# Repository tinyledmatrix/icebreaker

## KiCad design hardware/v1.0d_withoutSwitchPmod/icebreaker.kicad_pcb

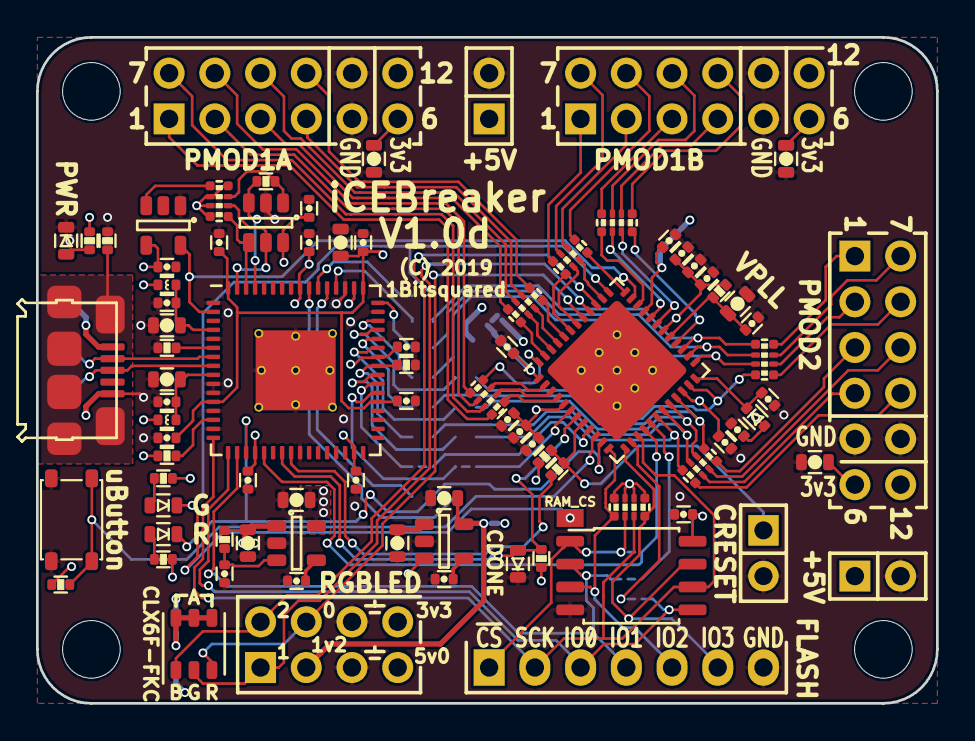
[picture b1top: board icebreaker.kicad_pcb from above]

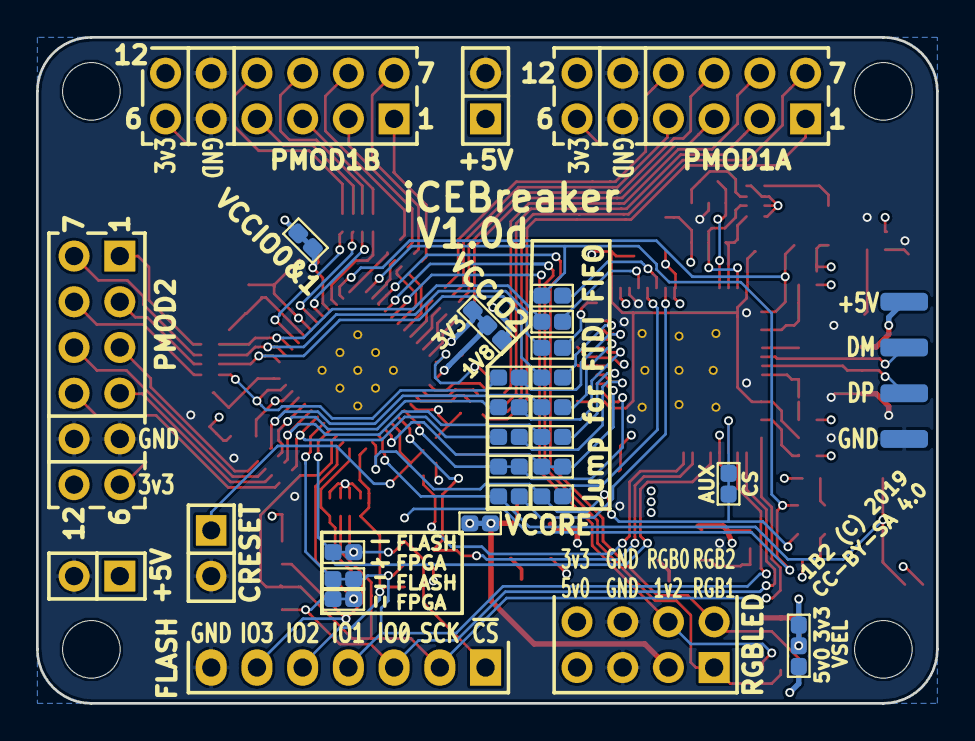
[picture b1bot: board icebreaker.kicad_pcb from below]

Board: 4 copper layers, 50.0 x 37.0 mm, 112 parts (25 on the bottom side), 112 nets.

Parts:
C1, C4, C10, C12, C13, C14, C16, C17, C18, C19, C20, C21, C22, C25, C26, C27, C29, C30, C31, C37: 100n; C_0402
C2, C5, C6, C7, C8, C9, C15: 4u7; C_0603
C3, C11, C28, C38: 10n; C_0402
C23, C36, C39: 1u; C_0402
C24: 10u; C_0603
C32, C33, C34: DNP; C_0603
C35: DNP; C_0402
D1, D4: GRN; D_0603
D2: ~~800mVf; D_SOD-523
D3: BLU; D_0603
D5: RED; D_0603
D11: LED_RGB; LED_Cree_PLCC6_3.4x3.4mm
J1, J2, J15, J16, J18, J29: Jumper; J_NC_0603_15
J3, J4, J5, J6, J7, J8, J9, J10, J11, J12, J13: Jumper; J_0603
J14, J19: Jumper; J_NC_0603_30
J17, J30: Jumper; J_NCNO_0903_30
J20: Flash; Pin_Header_Straight_1x07
J21, J22: PMOD; Socket_Strip_Angled_2x06
J23: PMOD; Socket_Strip_Straight_2x06
J25: RGB Led; Pin_Header_Straight_2x04
J26, J27: 5V AUX; Pin_Header_Straight_2x01
J28: CRESET; PinHeader_2x01_P2.54mm_Vertical
L1, L2: 600; L_0402
P1: pkl_USB_OTG; Connector_USB_Micro_B_SMD
P2, P3, P4, P5: UP; PAD_SMD_1x2.65
P6: RAM_CS; PAD_SMD_1x1.5
R1: 1M; R_0402
R2, R11: 10k; R_Array_Convex_4x0402
R3, R9, R13, R19, R25: 10k; R_0402
R4, R20, R21, R22, R23, R24: 33E; R_Array_Convex_4x0402
R5, R14, R15: 330E; R_0402
R6, R12, R26: 2k2; R_0402
R8: 12k; R_0402
R10: 100E; R_0402
SW1: TACT; SW_SPST_3x4x2.5
U1: 93C46B-SOT-23-6; SOT-23-6
U2: 3.3V; SOT-23-5
U3: 1V2; SOT-23-5
U4: FT2232H; QFN-64-4.45mm1EP_9x9mm_Pitch0.5mm
U5: W25Q; SOIC-8_5.3x5.3mm_Pitch1.27mm
U6: ICE5LP4K-SG48; QFN-48-1EP_7x7mm_Pitch0.5mm
U7: 12MHz; SOT-23-5

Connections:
+1V2: C15.1, J14.2, J25.3, U3.5
+1V8: C7.1, C10.1, C14.1, C16.1, C17.1, J17.3, U4.12, U4.37, U4.49, U4.64
+3V3: C1.1, C4.1, C5.1, C18.1, C19.1, C20.1, C21.1, C22.1, C29.1, C32.2, C33.2, C34.2, D2.A, J17.1, J19.2, J21.6, J21.12, J22.6, J22.12, J23.6, J23.12, J25.8, J30.1, L1.1, L2.1, R2.2, R2.4, R2.6, R2.7, R5.1, R9.2, R11.1, R11.3, R11.5, R11.7, R12.1, R13.2, R14.2, R15.2, R19.1, U1.6, U2.5, U4.20, U4.31, U4.42, U4.50, U4.56, U5.8, U7.4
+5V: C2.1, C8.1, J25.7, J26.1, J27.1, J30.3, P1.1, P2.1, R3.1, U2.1, U3.1, U3.3
/FLASH_CS: J18.1, J20.1, R11.6, U5.1
/FLASH_MISO|IO1: J16.2, J20.4, U4.18, U5.2
/FLASH_MOSI|IO0: J15.1, J20.3, U4.17, U5.5
/FLASH_~HLD~|~RST~|IO3: J20.6, R11.2, U5.7, U6.13
/FLASH_~WP~|IO2: J20.5, R11.8, U5.3, U6.12
/FTDI_CLK: U4.2, U6.35, U7.5
/P1A1: R20.1, U6.4
/P1A1x: J21.1, R20.2
/P1A2: R20.5, U6.2
/P1A2x: J21.2, R20.6
/P1A3: R23.1, U6.47
/P1A3x: J21.3, R23.2
/P1A4: R23.5, U6.45
/P1A4x: J21.4, R23.6
/P1A7: R20.3, U6.3
/P1A7x: J21.7, R20.4
/P1A8: R20.7, U6.48
/P1A8x: J21.8, R20.8
/P1A9: R23.3, U6.46
/P1A9x: J21.9, R23.4
/P1A10: R23.7, U6.44
/P1A10x: J21.10, R23.8
/P1B1: R21.1, U6.43
/P1B1x: J22.1, R21.2
/P1B2: R21.5, U6.38
/P1B2x: J22.2, R21.6
/P1B3: R24.1, U6.34
/P1B3x: J22.3, R24.2
/P1B4: R24.5, U6.31
/P1B4x: J22.4, R24.6
/P1B7: R21.3, U6.42
/P1B7x: J22.7, R21.4
/P1B8: R21.7, U6.36
/P1B8x: J22.8, R21.8
/P1B9: R24.3, U6.32
/P1B9x: J22.9, R24.4
/P1B10: R24.7, U6.28
/P1B10x: J22.10, R24.8
/P2_1: J10.2, R4.1, U6.27
/P2_1x: J23.1, R4.2
/P2_2: J8.2, R4.5, U6.25
/P2_2x: J23.2, R4.6
/P2_3: J6.2, R22.1, U6.21
/P2_3x: J23.3, R22.2
/P2_4: J4.2, R22.5, U6.19
/P2_4x: J23.4, R22.6
/P2_7: J9.2, R4.3, U6.26
/P2_7x: J23.7, R4.4
/P2_8: J7.2, R4.7, U6.23
/P2_8x: J23.8, R4.8
/P2_9: J5.2, R22.3, U6.20
/P2_9x: J23.9, R22.4
/P2_10: J3.2, R22.7, U6.18
/P2_10x: J23.10, R22.8
/Rx_TTL|FIFO_D0: J1.2, U6.6
/SPI_CS: J29.1, U4.19
/Tx_TTL|FIFO_D1: J2.2, U6.9
/USB_DM: P1.2, P3.1, U4.7
/USB_DP: P1.3, P4.1, U4.8
/VCCIO_0|1: C30.1, C31.1, J19.1, U6.22, U6.33
/VCCIO_2: C27.2, J17.2, U6.1
/VCCPLL: C24.1, C26.1, R10.1, U6.29
/VCORE: C23.1, C25.1, C28.1, C36.1, C37.1, C38.1, J14.1, R10.2, U6.5, U6.30
/VPP_2V5: C35.1, D2.C, U6.24
/iCE_CDONE: D3.A, R12.2, U4.23, U6.7
/iCE_CRESET: J28.1, R19.2, R26.1, U6.8
/iCE_SCK: J20.2, R11.4, U4.16, U5.6, U6.15
/iCE_SI: J16.1, U6.17
/iCE_SO: J15.2, U6.14
/iCE_SS_B: J18.2, U4.21, U6.16
/shield: P1.GND, R1.2
/xFIFO_D0: J1.1, U4.38
/xFIFO_D1: J2.1, U4.39
/xFIFO_D2: J3.1, U4.40
/xFIFO_D3: J4.1, R25.1, U4.41
/xFIFO_D4: J5.1, U4.43
/xFIFO_D5: J6.1, U4.44
/xFIFO_D6: J7.1, U4.45
/xFIFO_D7: J8.1, U4.46
/xFIFO_WKUP: J13.1, U4.55
/xFIFO_~RD: J11.1, U4.53
/xFIFO_~RXF: J9.1, U4.48
/xFIFO_~TXE: J10.1, U4.52
/xFIFO_~WR: J12.1, U4.54
/xiCE_CRESET: R26.2, U4.24
/~BUTTON: J13.2, R13.1, SW1.1, U6.10
/~LEDG: D4.C, J12.2, P6.1, U6.37
/~LEDR: D5.C, J11.2, J29.2, U6.11
/~LED_RGB0: D11.3, J25.4, U6.41
/~LED_RGB1: D11.2, J25.1, U6.40
/~LED_RGB2: D11.1, J25.2, U6.39
GND: C1.2, C2.2, C3.2, C4.2, C5.2, C6.2, C7.2, C8.2, C9.2, C10.2, C11.2, C12.2, C13.2, C14.2, C15.2, C16.2, C17.2, C18.2, C19.2, C20.2, C21.2, C22.2, C23.2, C24.2, C25.2, C26.2, C27.1, C28.2, C29.2, C30.2, C31.2, C32.1, C33.1, C34.1, C35.2, C36.2, C37.2, C38.2, C39.2, D1.C, D3.C, J20.7, J21.5, J21.11, J22.5, J22.11, J23.5, J23.11, J25.5, J25.6, J26.2, J27.2, J28.2, P1.5, P5.1, R1.1, R8.2, R25.2, SW1.2, U1.2, U2.2, U3.2, U4.1, U4.5, U4.10, U4.11, U4.13, U4.15, U4.25, U4.35, U4.47, U4.51, U4.65, U5.4, U6.49, U7.1
unnamed: C3.1, U2.4
unnamed: C11.1, U3.4
unnamed: C6.1, C12.1, L2.2, U4.4
unnamed: C9.1, C13.1, L1.2, U4.9
unnamed: C39.1, R3.2, U2.3
unnamed: D1.A, R5.2
unnamed: D4.A, R14.1
unnamed: D5.A, R15.1
unnamed: D11.4, D11.5, D11.6, J30.2
unnamed: R2.1, U1.4, U4.62
unnamed: R2.3, U1.5, U4.63
unnamed: R2.5, R6.2, U1.1
unnamed: R2.8, U7.3
unnamed: R6.1, U1.3, U4.61
unnamed: R8.1, U4.6
unnamed: R9.1, U4.14

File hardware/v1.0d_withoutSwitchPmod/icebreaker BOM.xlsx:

Id | Designator | Package | Quantity | Designation | MFc# | MFC | ALT-MFC# | ALT-MFC | Supplier and ref | LCSC
1 | J29,J15,J18,J16,J2,J1 | J_NC_0603_15 | 6 | Jumper
2 | U6 | QFN-48-1EP_7x7mm_Pitch0.5mm | 1 | ICE5LP4K-SG48 | ICE40UP5K-SG48I | Lattice |  |  |  | NA |  | https://octopart.com/search?q=iCE40UP5K
3 | U4 | QFN-64-4.45mm1EP_9x9mm_Pitch0.5mm | 1 | FT2232H | FT2232HQ-TRAY | FTDI |  |  |  | NA |  | https://octopart.com/ft2232hq-tray-ftdi-19172158?r=sp&s=PmpX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
4 | C32,C34,C33 | C_0603 | 3 | DNP
5 | C15,C8,C2,C5,C9,C6,C7 | C_0603 | 7 | 4u7 |  |  |  |  |  | 0603B475K100NT
6 | C24 | C_0603 | 1 | 10u |  |  |  |  |  | GRM188Z71A106MA73D
7 | D1,D4 | D_0603 | 2 | GRN |  |  |  |  | vorhanden
8 | D3 | D_0603 | 1 | BLU |  |  |  |  | vorhanden
9 | D5 | D_0603 | 1 | RED |  |  |  |  | vorhanden
10 | R1 | R_0402 | 1 | 1M |  |  |  |  |  | RC0402FR-071ML
11 | R5,R14,R15 | R_0402 | 3 | 330E |  |  |  |  |  | RC0402FR-07330RL
12 | R6,R12,R26 | R_0402 | 3 | 2k2 |  |  |  |  |  | RC0402FR-072K2L
13 | R8 | R_0402 | 1 | 12k |  |  |  |  |  | RC0402FR-0712KL
14 | R9,R13,R19,R3,R25 | R_0402 | 5 | 10k |  |  |  |  | wahrscheinlich vorhanden | RC0402FR-0710KL
15 | R10 | R_0402 | 1 | 100E |  |  |  |  |  | RC0402FR-07100RL
16 | L1,L2 | L_0402 | 2 | 600 |  |  |  |  |  | SZ1005K750TF
17 | C22,C21,C20,C18,C17,C14,C13,C12,C10,C16,C30,C31,C29,C27,C26,C25,C19,C1,C4,C37 | C_0402 | 20 | 100n |  |  |  |  | wahrscheinlich vorhanden | CC0402KRX7R7BB104
18 | C11,C28,C3,C38 | C_0402 | 4 | 10n |  |  |  |  |  | CC0402KRX7R7BB103
19 | C23,C36,C39 | C_0402 | 3 | 1u |  |  |  |  |  | 0402B105K100NT
20 | C35 | C_0402 | 1 | DNP
21 | U1 | SOT-23-6 | 1 | 93C46B-SOT-23-6 | 93LC46BT-E/OT | Microchip |  |  |  |  |  | https://octopart.com/93lc46bt-i%2Fsn-microchip-452705?r=sp&s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
22 | U2 | SOT-23-5 | 1 | 3.3V | SGM2028-3.3YN5G/TR | SGMIICRO |  |  | vorhanden (Ersatztyp) | SGM2028-3.3YN5G/TR
23 | U3 | SOT-23-5 | 1 | 1V2 | SGM2019-1.2YN5G/TR | SGMICRO |  |  |  | SGM2019-1.2YN5G/TR
24 | P1 | Connector_USB_Micro_B_SMD | 1 | pkl_USB_OTG |  |  |  |  | vorhanden
25 | U5 | SOIC-8_5.3x5.3mm_Pitch1.27mm | 1 | W25Q | W25Q128JVSIQ | Winbond |  |  |  | W25Q128JVSIQ
26 | U7 | SOT-23-5 | 1 | 12MHz | SIT2001BI-S2-33E-12.000000G | SiTime |  |  |  | NA
27 | P4,P3,P2,P5 | PAD_SMD_1x2.65 | 4 | UP
28 | J28 | PinHeader_2x01_P2.54mm_Vertical | 1 | CRESET |  |  |  |  | vorhanden (Ersatztyp)
29 | SW1 | SW_SPST_3x4x2.5 | 1 | TACT | SKRPABE010 | Alps |  |  |  | https://lcsc.com/product-detail/Tactile-Switches_ALPS_SKRPAB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
30 | P6 | PAD_SMD_1x1.5 | 1 | RAM_CS
31 | J13,J11,J9,J8,J7,J6,J5,J4,J3,J10,J12 | J_0603 | 11 | Jumper
32 | J14,J19 | J_NC_0603_30 | 2 | Jumper
33 | J17,J30 | J_NCNO_0903_30 | 2 | Jumper
34 | D2 | D_SOD-523 | 1 | ~~800mVf | CDBU0520 ??? |  |  |  | wahrscheinlich vorhanden
35 | R11,R2 | R_Array_Convex_4x0402 | 2 | 10k | YC124-FR-0710KL | Yageo |  |  |  | YC124-FR-0710KL
36 | R20,R4,R21,R22,R24,R23 | R_Array_Convex_4x0402 | 6 | 33E | YC124-FR-0710KL | Yageo |  |  |  | YC124-FR-0733RL
37 | D11 | LED_Cree_PLCC6_3.4x3.4mm | 1 | LED_RGB | FM-Z3535RGBA-SH | Foshan NationStar Optoelectronics | LTSN-D353EGBW | Lite-On |  | FM-Z3535RGBA-SH
38 | REF**,REF**,REF**,REF** | MountingHole_3-5mm | 4 | MH3
39 | J20 | Pin_Header_Straight_1x07 | 1 | Flash
40 | J25 | Pin_Header_Straight_2x04 | 1 | RGB Led
41 | J27,J26 | Pin_Header_Straight_2x01 | 2 | 5V AUX
42 | J23 | Socket_Strip_Straight_2x06 | 1 | PMOD |  |  |  |  | vorhanden (Ersatztyp) |  |  | zu Pos 43 ergänst -> alle P-mods gleich
43 | J22,J21, J23 | Socket_Strip_Angled_2x06 | 2 | PMOD |  |  |  |  |  | A2541HWR-2x6P
 |  |  | v

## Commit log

2019-06-27 deleted button board.
    Just delted that little button board for cheaper pcb-mfc
    Also added personal notes to BOM-xlsx

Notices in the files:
hardware/v1.0d_withoutSwitchPmod/icebreaker.kicad_pcb:
(C) 2019 Piotr Esden-Tempski
(C) 2019 1BitSquared
License: CC-BY-SA 4.0
1B2 (C) 2019
CC-BY-SA 4.0
(C) 2019
